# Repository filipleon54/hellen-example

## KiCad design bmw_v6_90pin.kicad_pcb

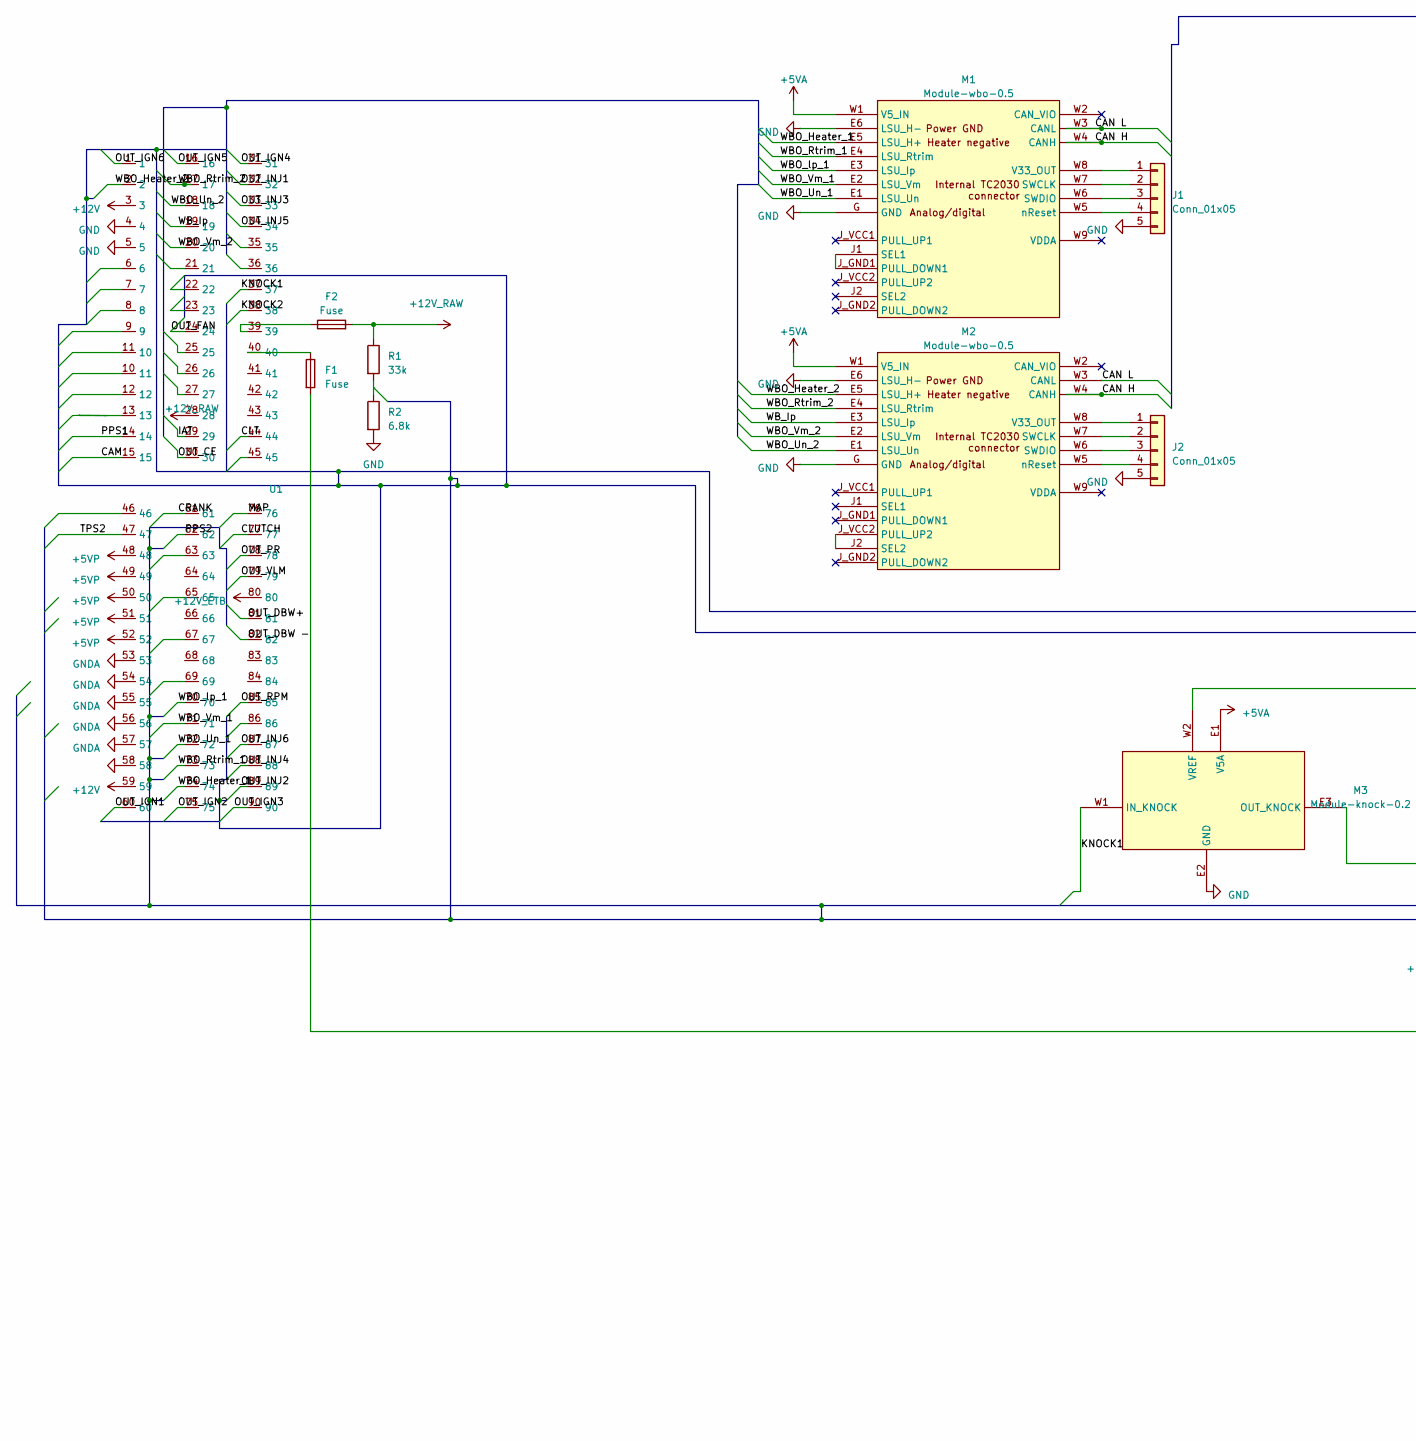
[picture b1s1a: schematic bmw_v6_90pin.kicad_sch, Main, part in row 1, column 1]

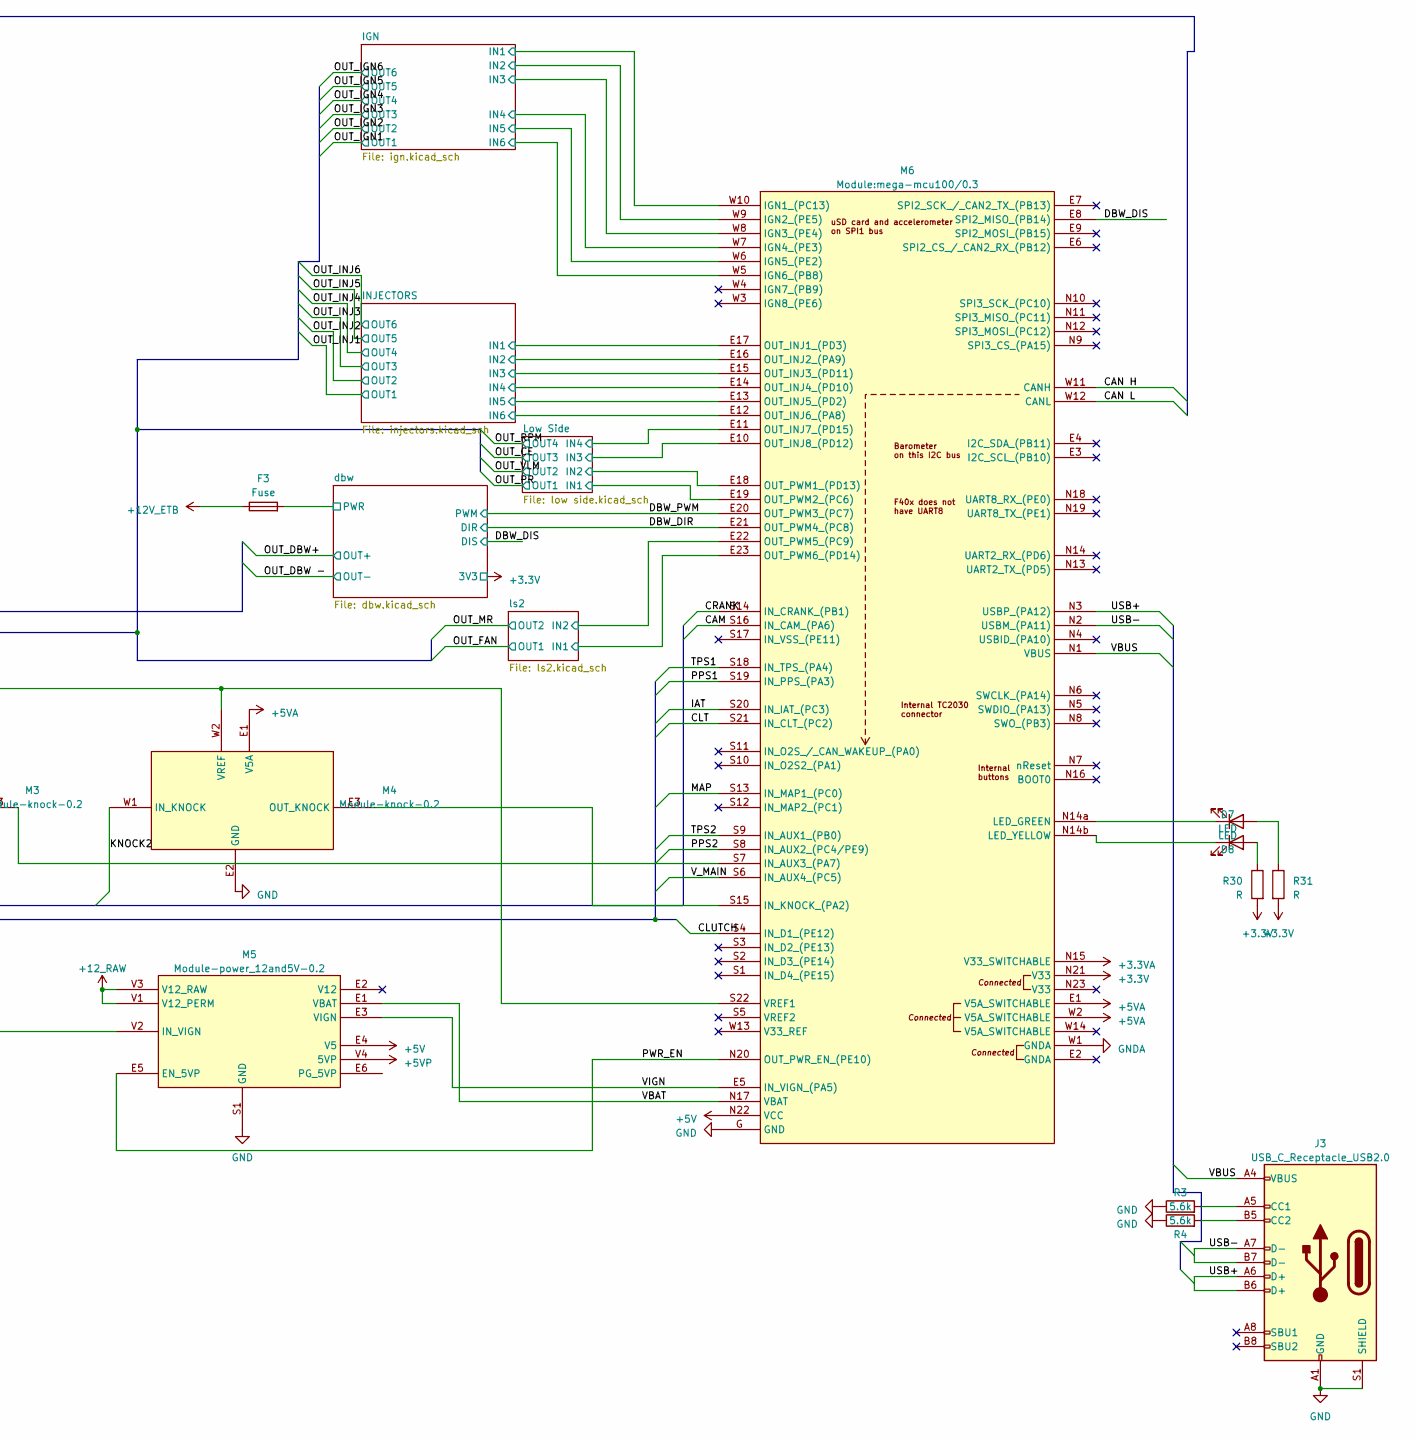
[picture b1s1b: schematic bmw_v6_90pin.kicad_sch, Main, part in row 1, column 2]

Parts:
D7, D8: LED; LED-0603
F1, F2, F3: Fuse; Fuse_1206_3216Metric
J1, J2: Conn_01x05; PinHeader_1x05_P2.54mm_Vertical
J3: USB_C_Receptacle_USB2.0; USB_C_Receptacle_Amphenol_12401610E4-2A
M1, M2: Module-wbo-0.5; wbo
M3, M4: Module-knock-0.2; knock
M5: Module-power_12and5V-0.2; power_12and5V
M6: Module:mega-mcu100/0.3; mega-mcu100
R1: 33k; R_0603_1608Metric
R2: 6.8k; R0603
R3, R4: 5.6k; R_0603_1608Metric
R30, R31: R; R0603
U1: 90_pin_ecu

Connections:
+3.3V: M6.N21 (V33), R30.2, R31.2; also elsewhere on the board
+3.3VA: M6.N15 (V33_SWITCHABLE)
+5V: M5.E4 (V5), M6.N22 (VCC)
+5VA: M1.W1 (V5_IN), M2.W1 (V5_IN), M3.E1 (V5A), M4.E1 (V5A), M6.E1 (V5A_SWITCHABLE), M6.W2 (V5A_SWITCHABLE)
+5VP: M5.V4 (5VP), U1.48, U1.49, U1.50, U1.51, U1.52
+12V_ETB: F3.1, U1.80
/CAM: M6.S16 (IN_CAM_(PA6)), U1.15
/CAN H: M1.W4 (CANH), M2.W4 (CANH), M6.W11 (CANH)
/CAN L: M1.W3 (CANL), M2.W3 (CANL), M6.W12 (CANL)
/CLT: M6.S21 (IN_CLT_(PC2)), U1.44
/CLUTCH: M6.S4 (IN_D1_(PE12)), U1.77
/CRANK: M6.S14 (IN_CRANK_(PB1)), U1.61
/DBW_DIR: M6.E21 (OUT_PWM4_(PC8)); also elsewhere on the board
/DBW_DIS: M6.E8 (SPI2_MISO_(PB14)); also elsewhere on the board
/DBW_PWM: M6.E20 (OUT_PWM3_(PC7)); also elsewhere on the board
/IAT: M6.S20 (IN_IAT_(PC3)), U1.29
/IGN/IN1: M6.W10 (IGN1_(PC13)); also elsewhere on the board
/IGN/IN2: M6.W9 (IGN2_(PE5)); also elsewhere on the board
/IGN/IN3: M6.W8 (IGN3_(PE4)); also elsewhere on the board
/IGN/IN4: M6.W7 (IGN4_(PE3)); also elsewhere on the board
/IGN/IN5: M6.W6 (IGN5_(PE2)); also elsewhere on the board
/IGN/IN6: M6.W5 (IGN6_(PB8)); also elsewhere on the board
/INJECTORS/IN1: M6.E17 (OUT_INJ1_(PD3)); also elsewhere on the board
/INJECTORS/IN2: M6.E16 (OUT_INJ2_(PA9)); also elsewhere on the board
/INJECTORS/IN3: M6.E15 (OUT_INJ3_(PD11)); also elsewhere on the board
/INJECTORS/IN4: M6.E14 (OUT_INJ4_(PD10)); also elsewhere on the board
/INJECTORS/IN5: M6.E13 (OUT_INJ5_(PD2)); also elsewhere on the board
/INJECTORS/IN6: M6.E12 (OUT_INJ6_(PA8)); also elsewhere on the board
/KNOCK1: M3.W1 (IN_KNOCK), U1.37
/KNOCK2: M4.W1 (IN_KNOCK), U1.38
/Low Side/IN1: M6.E19 (OUT_PWM2_(PC6)); also elsewhere on the board
/Low Side/IN2: M6.E18 (OUT_PWM1_(PD13)); also elsewhere on the board
/Low Side/IN3: M6.E10 (OUT_INJ8_(PD12)); also elsewhere on the board
/Low Side/IN4: M6.E11 (OUT_INJ7_(PD15)); also elsewhere on the board
/MAP: M6.S13 (IN_MAP1_(PC0)), U1.76
/OUT_CE: U1.30; also elsewhere on the board
/OUT_DBW -: U1.82; also elsewhere on the board
/OUT_DBW+: U1.81; also elsewhere on the board
/OUT_FAN: U1.24; also elsewhere on the board
/OUT_IGN1: U1.60; also elsewhere on the board
/OUT_IGN2: U1.75; also elsewhere on the board
/OUT_IGN3: U1.90; also elsewhere on the board
/OUT_IGN4: U1.31; also elsewhere on the board
/OUT_IGN5: U1.16; also elsewhere on the board
/OUT_IGN6: U1.1; also elsewhere on the board
/OUT_INJ1: U1.32; also elsewhere on the board
/OUT_INJ2: U1.89; also elsewhere on the board
/OUT_INJ3: U1.33; also elsewhere on the board
/OUT_INJ4: U1.88; also elsewhere on the board
/OUT_INJ5: U1.34; also elsewhere on the board
/OUT_INJ6: U1.87; also elsewhere on the board
/OUT_PR: U1.78; also elsewhere on the board
/OUT_RPM: U1.85; also elsewhere on the board
/OUT_VLM: U1.79; also elsewhere on the board
/PPS1: M6.S19 (IN_PPS_(PA3)), U1.14
/PPS2: M6.S8 (IN_AUX2_(PC4/PE9)), U1.62
/PWR_EN: M5.E5 (EN_5VP), M6.N20 (OUT_PWR_EN_(PE10))
/TPS1: M6.S18 (IN_TPS_(PA4))
/TPS2: M6.S9 (IN_AUX1_(PB0)), U1.47
/USB+: J3.A6 (D+), J3.B6 (D+), M6.N3 (USBP_(PA12))
/USB-: J3.A7 (D-), J3.B7 (D-), M6.N2 (USBM_(PA11))
/VBAT: M5.E1 (VBAT), M6.N17 (VBAT)
/VBUS: J3.A4 (VBUS), J3.A9 (VBUS), J3.B4 (VBUS), J3.B9 (VBUS), M6.N1 (VBUS)
/VIGN: M5.E3 (VIGN), M6.E5 (IN_VIGN_(PA5))
/V_MAIN: M6.S6 (IN_AUX4_(PC5))
/WBO_Heater_1: M1.E5 (LSU_H+), U1.74
/WBO_Heater_2: M2.E5 (LSU_H+), U1.2
/WBO_Rtrim_1: M1.E4 (LSU_Rtrim), U1.73
/WBO_Rtrim_2: M2.E4 (LSU_Rtrim), U1.17
/WBO_Un_1: M1.E1 (LSU_Un), U1.72
/WBO_Un_2: M2.E1 (LSU_Un), U1.18
/WBO_Vm_1: M1.E2 (LSU_Vm), U1.71
/WBO_Vm_2: M2.E2 (LSU_Vm), U1.20
/WBO_lp_1: M1.E3 (LSU_Ip), U1.70
/WB_Ip: M2.E3 (LSU_Ip), U1.19
/dbw/PWR: F3.2; also elsewhere on the board
/ls2/IN1: M6.E23 (OUT_PWM6_(PD14)); also elsewhere on the board
/ls2/IN2: M6.E22 (OUT_PWM5_(PC9)); also elsewhere on the board
GND: J1.5, J2.5, J3.A1 (GND), J3.A12 (GND), J3.B1 (GND), J3.B12 (GND), J3.S1 (SHIELD), M1.E6 (LSU_H-), M1.G (GND), M2.E6 (LSU_H-), M2.G (GND), M3.E2 (GND), M4.E2 (GND), M5.S1 (GND), M6.G (GND), R2.2, R3.1, R4.1, U1.4, U1.5; also elsewhere on the board
GNDA: M6.W1 (GNDA), U1.53, U1.54, U1.55, U1.56, U1.57, U1.58
unnamed: D7.2 (A), R30.1
unnamed: D7.1 (K), M6.N14b (LED_YELLOW)
unnamed: D8.2 (A), R31.1
unnamed: D8.1 (K), M6.N14a (LED_GREEN)
unnamed: F1.1, U1.40
unnamed: F2.1, U1.39
unnamed: J1.1, M1.W8 (V33_OUT)
unnamed: J1.2, M1.W7 (SWCLK)
unnamed: J1.3, M1.W6 (SWDIO)
unnamed: J1.4, M1.W5 (nReset)
unnamed: J2.1, M2.W8 (V33_OUT)
unnamed: J2.2, M2.W7 (SWCLK)
unnamed: J2.3, M2.W6 (SWDIO)
unnamed: J2.4, M2.W5 (nReset)
unnamed: J3.A5 (CC1), R3.2
unnamed: J3.B5 (CC2), R4.2
unnamed: M1.J1 (SEL1), M1.J_GND1 (PULL_DOWN1)
unnamed: M2.J2 (SEL2), M2.J_VCC2 (PULL_UP2)
unnamed: M3.E3 (OUT_KNOCK), M6.S7 (IN_AUX3_(PA7))
unnamed: M3.W2 (VREF), M4.W2 (VREF), M6.S22 (VREF1)
unnamed: M4.E3 (OUT_KNOCK), M6.S15 (IN_KNOCK_(PA2))
unnamed: F1.2, M5.V2 (IN_VIGN)
unnamed: R1.2, R2.1

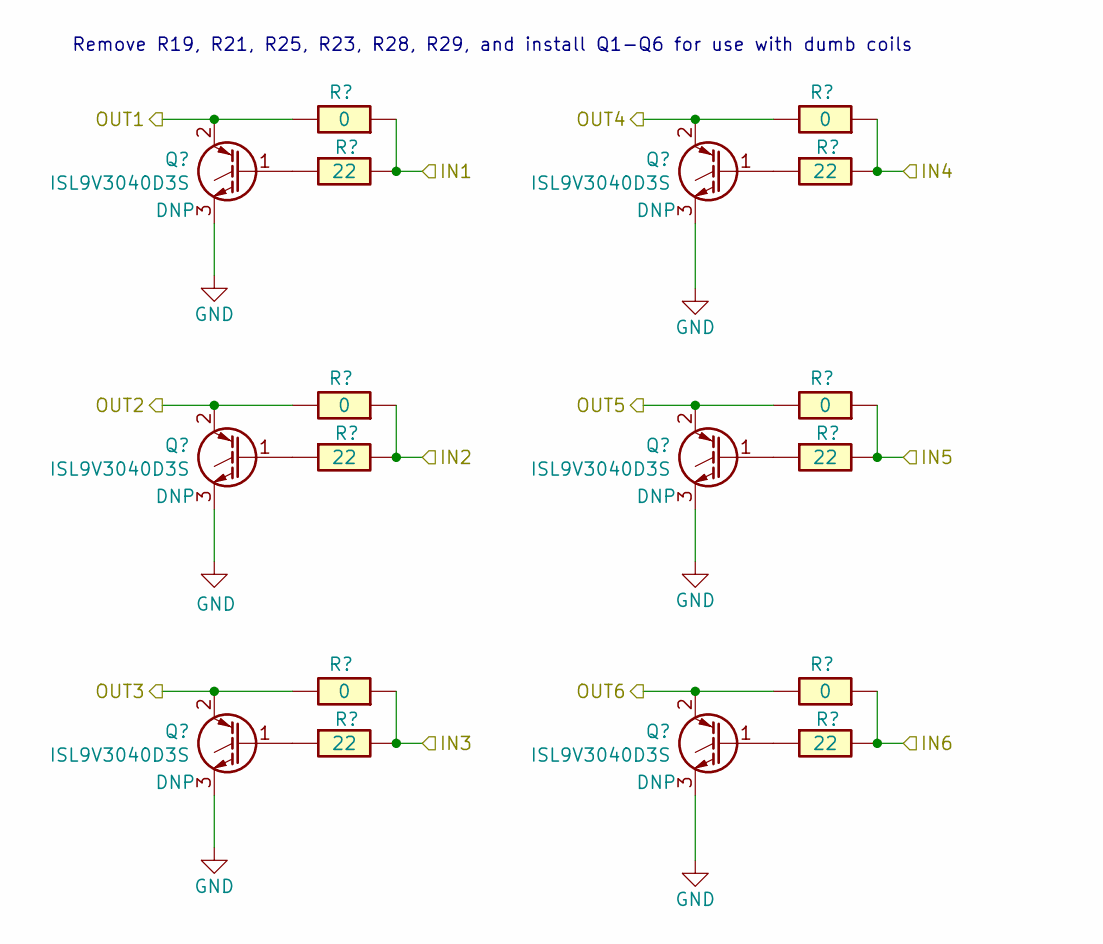
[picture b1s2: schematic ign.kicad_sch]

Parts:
Q7, Q8, Q9, Q10, Q11, Q12: ISL9V3040D3S; TO-252-2
R12, R13, R14, R18, R19, R20: 22; R0603; LCSC C23345
R15, R16, R17, R21, R22, R23: 0; R_2512_6332Metric; LCSC C25469

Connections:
/IGN/IN1: R12.2, R15.1; also elsewhere on the board
/IGN/IN2: R13.2, R16.1; also elsewhere on the board
/IGN/IN3: R14.2, R17.1; also elsewhere on the board
/IGN/IN4: R18.2, R21.1; also elsewhere on the board
/IGN/IN5: R19.2, R22.1; also elsewhere on the board
/IGN/IN6: R20.2, R23.1; also elsewhere on the board
/OUT_IGN1: Q7.2 (C), R15.2; also elsewhere on the board
/OUT_IGN2: Q8.2 (C), R16.2; also elsewhere on the board
/OUT_IGN3: Q9.2 (C), R17.2; also elsewhere on the board
/OUT_IGN4: Q10.2 (C), R21.2; also elsewhere on the board
/OUT_IGN5: Q11.2 (C), R22.2; also elsewhere on the board
/OUT_IGN6: Q12.2 (C), R23.2; also elsewhere on the board
GND: Q7.3 (E), Q8.3 (E), Q9.3 (E), Q10.3 (E), Q11.3 (E), Q12.3 (E); also elsewhere on the board
unnamed: Q7.1 (G), R12.1
unnamed: Q8.1 (G), R13.1
unnamed: Q9.1 (G), R14.1
unnamed: Q10.1 (G), R18.1
unnamed: Q11.1 (G), R19.1
unnamed: Q12.1 (G), R20.1

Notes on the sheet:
Remove R19, R21, R25, R23, R28, R29, and install Q1-Q6 for use with dumb coils

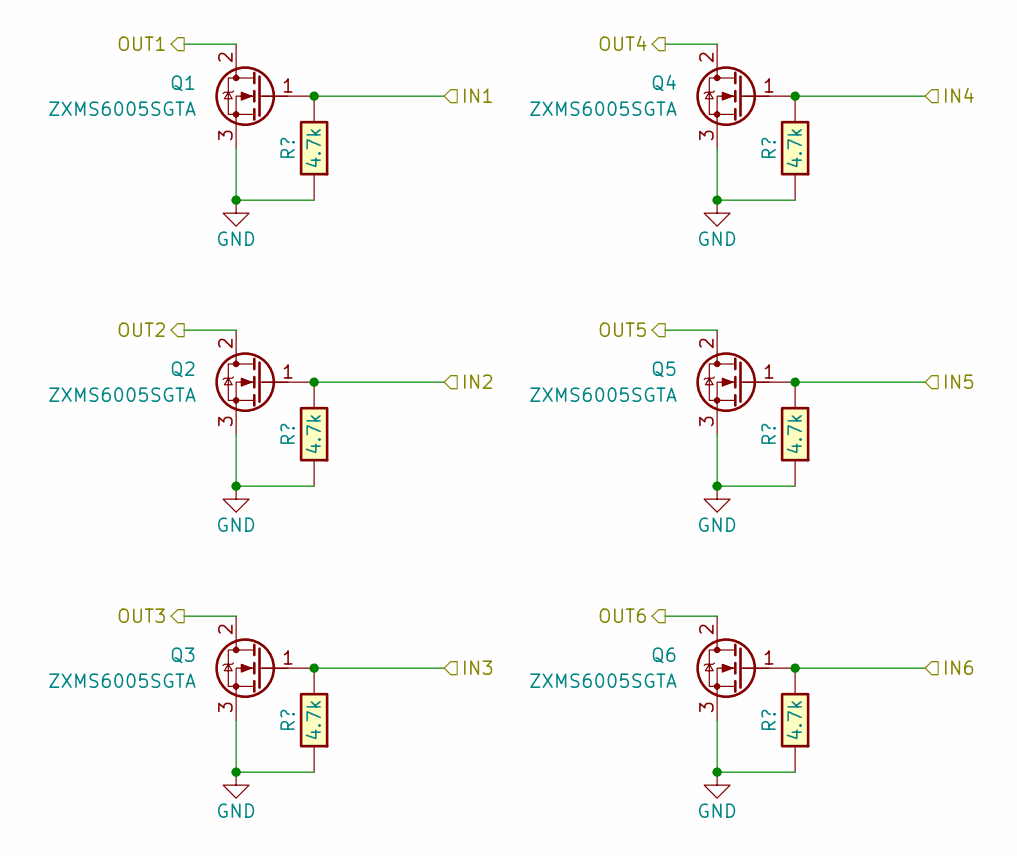
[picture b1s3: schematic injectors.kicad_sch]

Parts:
Q1, Q2, Q3, Q4, Q5, Q6: ZXMS6005SGTA; SOT-223; LCSC C174042
R6, R7, R8, R9, R10, R11: 4.7k; R0603; LCSC C23162

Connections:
/INJECTORS/IN1: Q1.1 (G), R6.2; also elsewhere on the board
/INJECTORS/IN2: Q2.1 (G), R7.2; also elsewhere on the board
/INJECTORS/IN3: Q3.1 (G), R8.2; also elsewhere on the board
/INJECTORS/IN4: Q4.1 (G), R9.2; also elsewhere on the board
/INJECTORS/IN5: Q5.1 (G), R10.2; also elsewhere on the board
/INJECTORS/IN6: Q6.1 (G), R11.2; also elsewhere on the board
/OUT_INJ1: Q1.2 (D); also elsewhere on the board
/OUT_INJ2: Q2.2 (D); also elsewhere on the board
/OUT_INJ3: Q3.2 (D); also elsewhere on the board
/OUT_INJ4: Q4.2 (D); also elsewhere on the board
/OUT_INJ5: Q5.2 (D); also elsewhere on the board
/OUT_INJ6: Q6.2 (D); also elsewhere on the board
GND: Q1.3 (S), Q2.3 (S), Q3.3 (S), Q4.3 (S), Q5.3 (S), Q6.3 (S), R6.1, R7.1, R8.1, R9.1, R10.1, R11.1; also elsewhere on the board

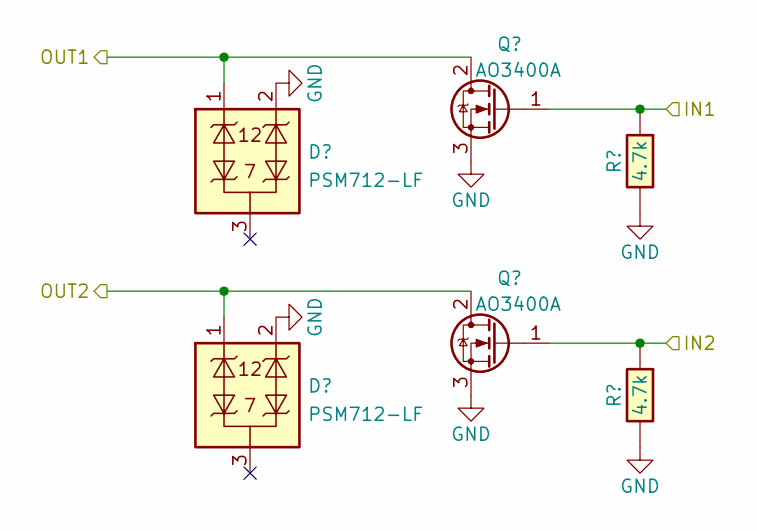
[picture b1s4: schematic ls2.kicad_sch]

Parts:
D5, D6: PSM712-LF; SOT-23; LCSC C32677
Q17, Q18: AO3400A; SOT-23; LCSC C20917
R28, R29: 4.7k; R0603; LCSC C23162

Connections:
/OUT_FAN: D5.1, Q17.2 (D); also elsewhere on the board
/OUT_MR: D6.1, Q18.2 (D)
/ls2/IN1: Q17.1 (G), R28.1; also elsewhere on the board
/ls2/IN2: Q18.1 (G), R29.1; also elsewhere on the board
GND: D5.2, D6.2, Q17.3 (S), Q18.3 (S), R28.2, R29.2; also elsewhere on the board

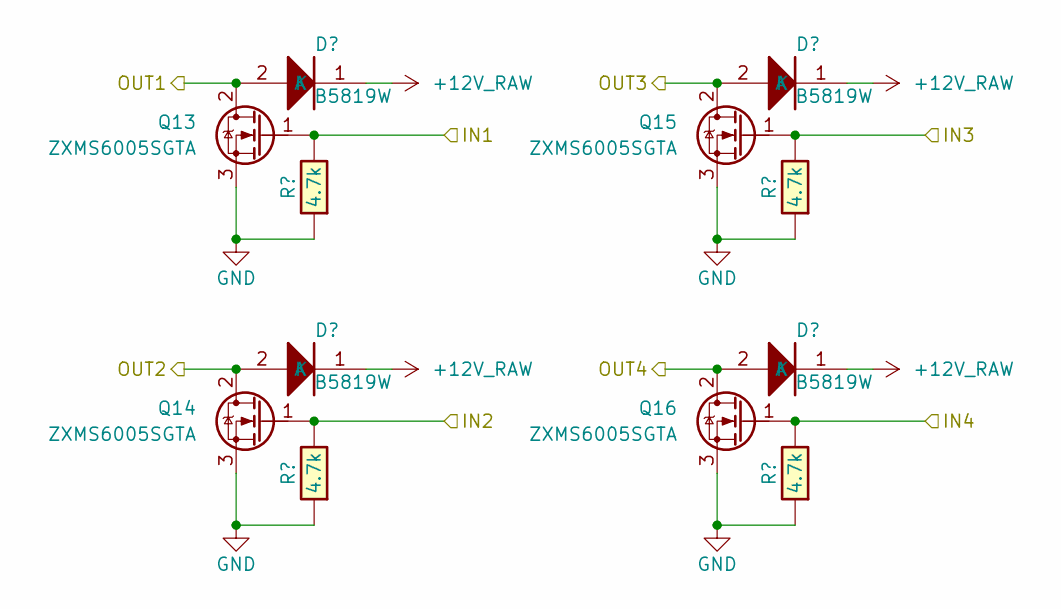
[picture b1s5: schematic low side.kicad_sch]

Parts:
D1, D2, D3, D4: B5819W; SOD-123; LCSC C8598
Q13, Q14, Q15, Q16: ZXMS6005SGTA; SOT-223; LCSC C174042
R24, R25, R26, R27: 4.7k; R0603; LCSC C23162

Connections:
+12V_RAW: D1.1 (K), D2.1 (K), D3.1 (K), D4.1 (K)
/Low Side/IN1: Q13.1 (G), R24.2; also elsewhere on the board
/Low Side/IN2: Q14.1 (G), R25.2; also elsewhere on the board
/Low Side/IN3: Q15.1 (G), R26.2; also elsewhere on the board
/Low Side/IN4: Q16.1 (G), R27.2; also elsewhere on the board
/OUT_CE: D3.2 (A), Q15.2 (D); also elsewhere on the board
/OUT_PR: D1.2 (A), Q13.2 (D); also elsewhere on the board
/OUT_RPM: D4.2 (A), Q16.2 (D); also elsewhere on the board
/OUT_VLM: D2.2 (A), Q14.2 (D); also elsewhere on the board
GND: Q13.3 (S), Q14.3 (S), Q15.3 (S), Q16.3 (S), R24.1, R25.1, R26.1, R27.1; also elsewhere on the board

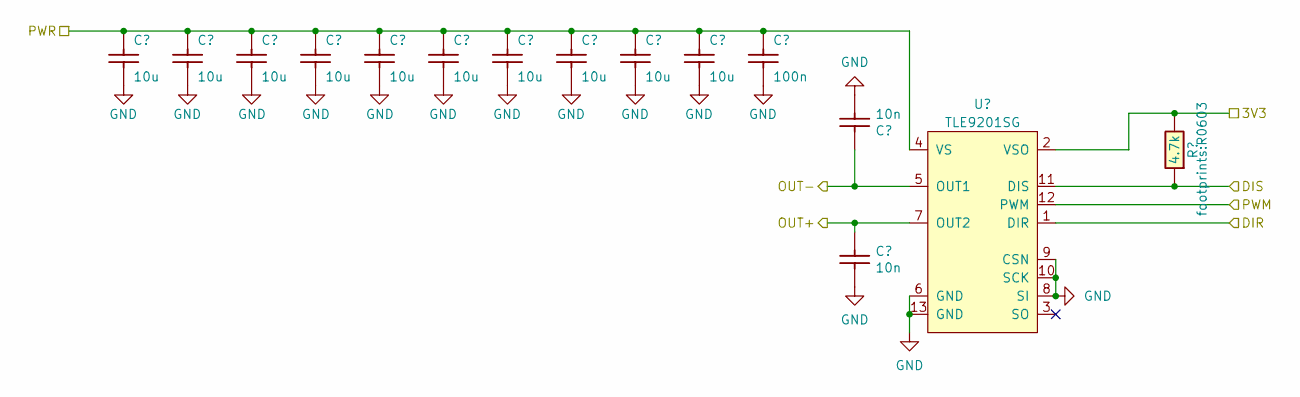
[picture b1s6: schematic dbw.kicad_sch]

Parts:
C1, C2, C3, C4, C5, C6, C7, C8, C9, C10: 10u; C0805; LCSC C15850
C11: 100n; C0805; LCSC C14663
C12, C13: 10n; C0603; LCSC C57112
R5: 4.7k; R0603; LCSC C23162
U2: TLE9201SG; Infineon_PG-DSO-12-11; LCSC C112633

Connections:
+3.3V: R5.2, U2.2 (VSO); also elsewhere on the board
/DBW_DIR: U2.1 (DIR); also elsewhere on the board
/DBW_DIS: R5.1, U2.11 (DIS); also elsewhere on the board
/DBW_PWM: U2.12 (PWM); also elsewhere on the board
/OUT_DBW -: C12.2, U2.5 (OUT1); also elsewhere on the board
/OUT_DBW+: C13.2, U2.7 (OUT2); also elsewhere on the board
/dbw/PWR: C1.2, C2.2, C3.2, C4.2, C5.2, C6.2, C7.2, C8.2, C9.2, C10.2, C11.2, U2.4 (VS); also elsewhere on the board
GND: C1.1, C2.1, C3.1, C4.1, C5.1, C6.1, C7.1, C8.1, C9.1, C10.1, C11.1, C12.1, C13.1, U2.6 (GND), U2.8 (SI), U2.9 (CSN), U2.10 (SCK), U2.13 (GND); also elsewhere on the board

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
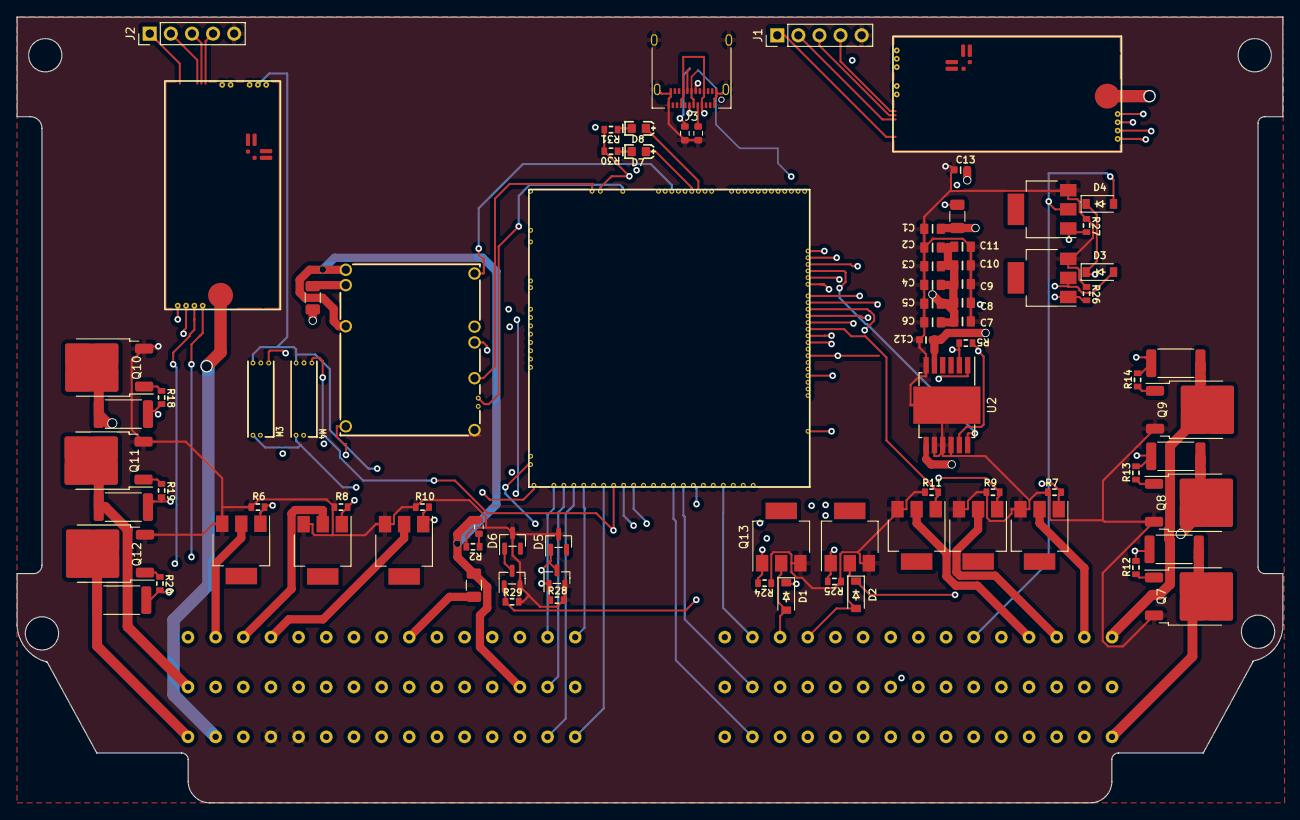
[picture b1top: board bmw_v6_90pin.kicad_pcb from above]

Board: 4 copper layers, 152.4 x 94.6 mm, 84 parts (0 on the bottom side), 109 nets.

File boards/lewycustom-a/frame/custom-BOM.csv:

Comment,Designator,Footprint,LCSC Part #
"10u","C1","C0805","C15850"
"10u","C2","C0805","C15850"
"10u","C3","C0805","C15850"
"10u","C4","C0805","C15850"
"10u","C5","C0805","C15850"
"10u","C6","C0805","C15850"
"10u","C7","C0805","C15850"
"10u","C8","C0805","C15850"
"10u","C9","C0805","C15850"
"10u","C10","C0805","C15850"
"100n","C11","C0805","C14663"
"10n","C12","C0603","C57112"
"10n","C13","C0603","C57112"
"B5819W","D1","SOD-123","C8598"
"B5819W","D2","SOD-123","C8598"
"B5819W","D3","SOD-123","C8598"
"B5819W","D4","SOD-123","C8598"
"PSM712-LF","D5","SOT-23","C32677"
"PSM712-LF","D6","SOT-23","C32677"
"LED","D7","LED-0603",""
"LED","D8","LED-0603",""
"Fuse","F1","Fuse_1206_3216Metric",""
"Fuse","F2","Fuse_1206_3216Metric",""
"Fuse","F3","Fuse_1206_3216Metric",""
"Conn_01x05","J1","PinHeader_1x05_P2.54mm_Vertical",""
"Conn_01x05","J2","PinHeader_1x05_P2.54mm_Vertical",""
"USB_C_Receptacle_USB2.0","J3","USB_C_Receptacle_Amphenol_12401610E4-2A",""
"Module:wbo/0.5","M1","wbo",""
"Module:wbo/0.5","M2","wbo",""
"Module:knock/0.2","M3","knock",""
"Module:knock/0.2","M4","knock",""
"Module:power_12and5V/0.2","M5","power_12and5V",""
"Module:mega-mcu100/0.3","M6","mega-mcu100",""
"ZXMS6005SGTA","Q1","SOT-223","C174042"
"ZXMS6005SGTA","Q2","SOT-223","C174042"
"ZXMS6005SGTA","Q3","SOT-223","C174042"
"ZXMS6005SGTA","Q4","SOT-223","C174042"
"ZXMS6005SGTA","Q5","SOT-223","C174042"
"ZXMS6005SGTA","Q6","SOT-223","C174042"
"ISL9V3040D3S","Q7","DPAK",""
"ISL9V3040D3S","Q8","DPAK",""
"ISL9V3040D3S","Q9","DPAK",""
"ISL9V3040D3S","Q10","DPAK",""
"ISL9V3040D3S","Q11","DPAK",""
"ISL9V3040D3S","Q12","DPAK",""
"ZXMS6005SGTA","Q13","SOT-223","C174042"
"ZXMS6005SGTA","Q14","SOT-223","C174042"
"ZXMS6005SGTA","Q15","SOT-223","C174042"
"ZXMS6005SGTA","Q16","SOT-223","C174042"
"AO3400A","Q17","SOT-23"," C20917"
"AO3400A","Q18","SOT-23"," C20917"
"33k","R1","R0603",""
"6.8k","R2","R0603",""
"5.6k","R3","R0603",""
"5.6k","R4","R0603",""
"4.7k","R5","R0603","C23162"
"4.7k","R6","R0603","C23162"
"4.7k","R7","R0603","C23162"
"4.7k","R8","R0603","C23162"
"4.7k","R9","R0603","C23162"
"4.7k","R10","R0603","C23162"
"4.7k","R11","R0603","C23162"
"22","R12","R0603","C23345"
"22","R13","R0603","C23345"
"22","R14","R0603","C23345"
"0","R15","R2512","C25469"
"0","R16","R2512","C25469"
"0","R17","R2512","C25469"
"22","R18","R0603","C23345"
"22","R19","R0603","C23345"
"22","R20","R0603","C23345"
"0","R21","R2512","C25469"
"0","R22","R2512","C25469"
"0","R23","R2512","C25469"
"4.7k","R24","R0603","C23162"
"4.7k","R25","R0603","C23162"
"4.7k","R26","R0603","C23162"
"4.7k","R27","R0603","C23162"
"4.7k","R28","R0603","C23162"
"4.7k","R29","R0603","C23162"
"R","R30","R0603",""
"R","R31","R0603",""
"~","U1","90_pin_ecu",""
"TLE9201SG","U2","Infineon_PG-DSO-12-11","C112633"

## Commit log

2024-01-27 Rename bmw_v6_90pin.kicad_pcb to lewycustom.kicad_pcb
2024-01-27 Rename bmw_v6_90pin.kicad_pro to lewycustom.kicad_pro
2024-01-27 Rename bmw_v6_90pin.kicad_sch to lewycustom.kicad_sch
2024-01-27 [skip actions] Auto-generated board v2.1
2024-01-28 Rename bmw_v6_90pin.kicad_prl to lewycustom.kicad_prl
